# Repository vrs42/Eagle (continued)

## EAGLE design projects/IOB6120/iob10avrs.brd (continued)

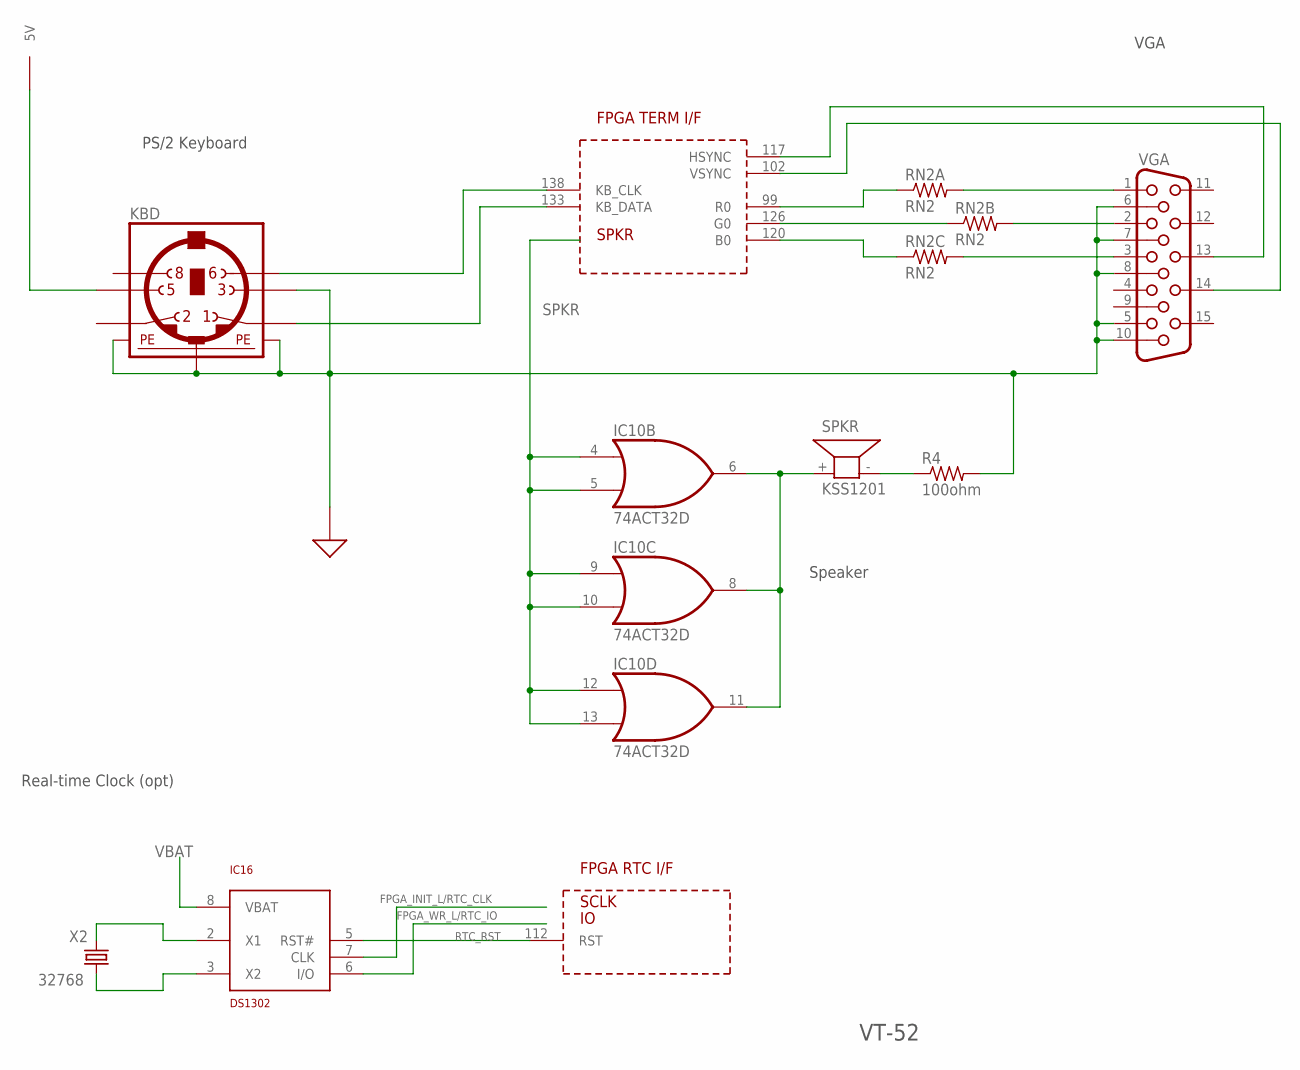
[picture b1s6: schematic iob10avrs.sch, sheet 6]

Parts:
IC10: 74ACT32D; SO14
IC12: XC2S100-5TQ144C; TQFP144
IC16: DS1302; SO08
KBD: MINI_DIN_6; M_DIN6
R4: 100ohm; M1206
RN2: RN2; RN-CTS-744C043
SPKR: KSS1201
VGA: HF15H; HDF15H
X2: 32768; TC26H

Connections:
2V5: IC12.9 (2V5), IC12.14 (2V5), IC12.24 (2V5), IC12.55 (2V5), IC12.82 (2V5), IC12.92 (2V5), IC12.97 (2V5), IC12.125 (2V5); also elsewhere on the board
5V: IC16.1 (5V), KBD.5; also elsewhere on the board
B0: IC12.120 (B0), RN2.3 (1)
FPGA_INIT_L/RTC_CLK: IC16.7 (CLK); also elsewhere on the board
FPGA_WR_L/RTC_IO: IC16.6 (I/O); also elsewhere on the board
G0: IC12.126 (G0), RN2.2 (1)
GND: IC12.8 (GND), IC12.17 (GND), IC12.25 (GND), IC12.33 (GND), IC12.45 (GND), IC12.52 (GND), IC12.61 (GND), IC12.73 (GND), IC12.81 (GND), IC12.89 (GND), IC12.98 (GND), IC12.110 (GND), IC12.119 (GND), IC12.128 (GND), IC12.135 (GND), IC12.143 (GND), IC16.4 (GND), KBD.3, KBD.SH1 (PE1), KBD.SH2 (PE2), KBD.SH3 (PE3), R4.2, VGA.5, VGA.6, VGA.7, VGA.8, VGA.10; also elsewhere on the board
HS: IC12.117 (HSYNC), VGA.13
KB_CLK: IC12.138 (KB_CLK), KBD.6
KB_DATA: IC12.133 (KB_DATA), KBD.1
unnamed: IC16.3 (X2), X2.1
unnamed: RN2.8 (2), VGA.1
unnamed: RN2.7 (2), VGA.2
unnamed: RN2.6 (2), VGA.3
unnamed: IC16.2 (X1), X2.2
unnamed: R4.1, SPKR.- (2)
R0: IC12.99 (R0), RN2.1
RTC_RST: IC12.112 (RST), IC16.5 (RST#)
SPEAKER: IC10.6 (O), IC10.8 (O), IC10.11 (O), SPKR.+ (1)
SPKR: IC10.4 (I0), IC10.5 (I1), IC10.9 (I0), IC10.10 (I1), IC10.12 (I0), IC10.13 (I1); also elsewhere on the board
VBAT: IC16.8 (VBAT); also elsewhere on the board
VCCO: IC12.1 (VCCO), IC12.16 (VCCO), IC12.35 (VCCO), IC12.36 (VCCO), IC12.53 (VCCO), IC12.70 (VCCO), IC12.71 (VCCO), IC12.90 (VCCO), IC12.107 (VCCO), IC12.108 (VCCO), IC12.127 (VCCO), IC12.144 (VCCO); also elsewhere on the board
VS: IC12.102 (VSYNC), VGA.14

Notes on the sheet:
VT-52
PS/2 Keyboard
VGA
Speaker
Real-time Clock (opt)

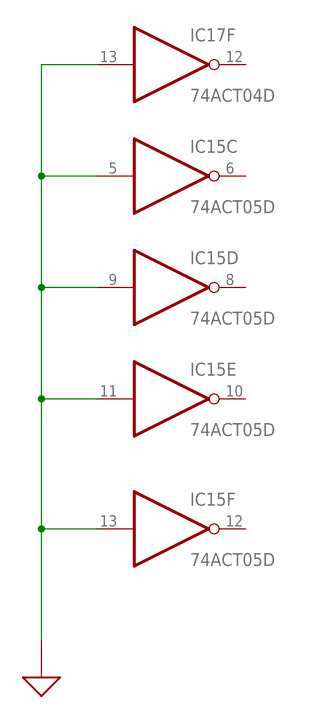
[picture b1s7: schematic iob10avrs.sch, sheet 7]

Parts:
IC15: 74ACT05D; SO14
IC17: 74ACT04D; SO14

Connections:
GND: IC15.5 (I), IC15.9 (I), IC15.11 (I), IC15.13 (I), IC17.13 (I); also elsewhere on the board

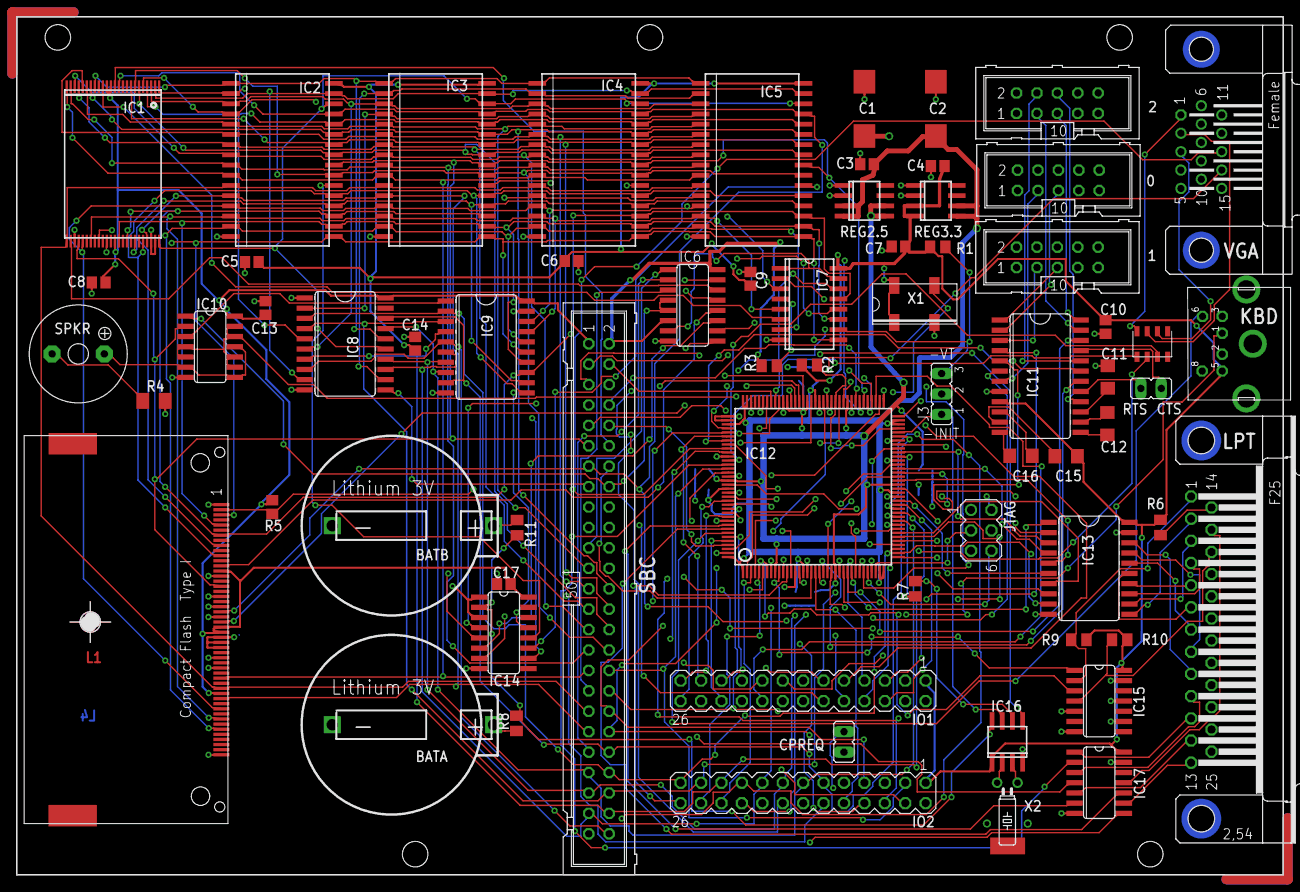
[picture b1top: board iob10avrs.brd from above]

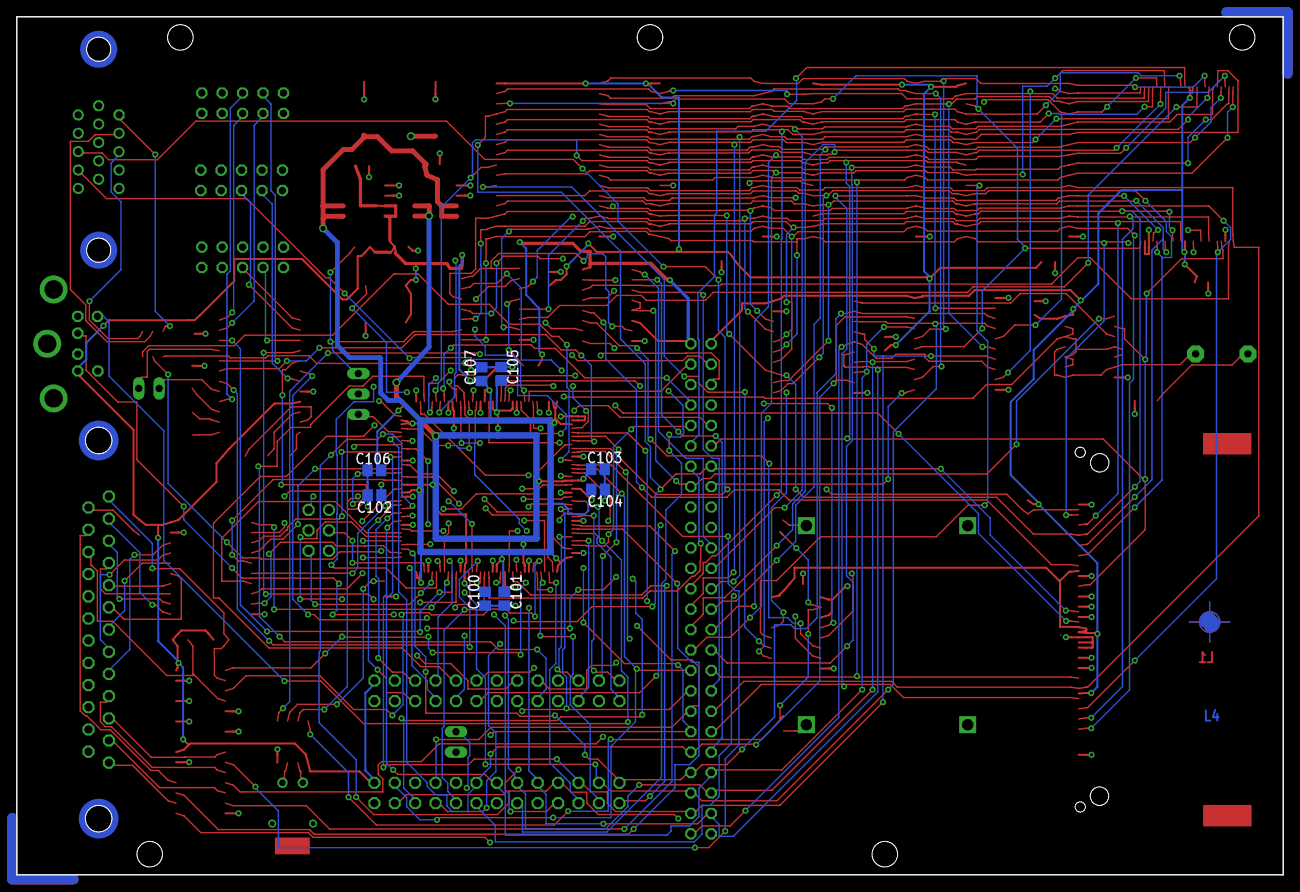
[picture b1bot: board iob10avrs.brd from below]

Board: 4 copper layers, 157.5 x 106.7 mm, 78 parts (8 on the bottom side), 196 nets.

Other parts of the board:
U$34: PASS-ROUND
U$42: ANGLE-ARROW-NW1-16
U$43: ANGLE-ARROW-SE1-16
